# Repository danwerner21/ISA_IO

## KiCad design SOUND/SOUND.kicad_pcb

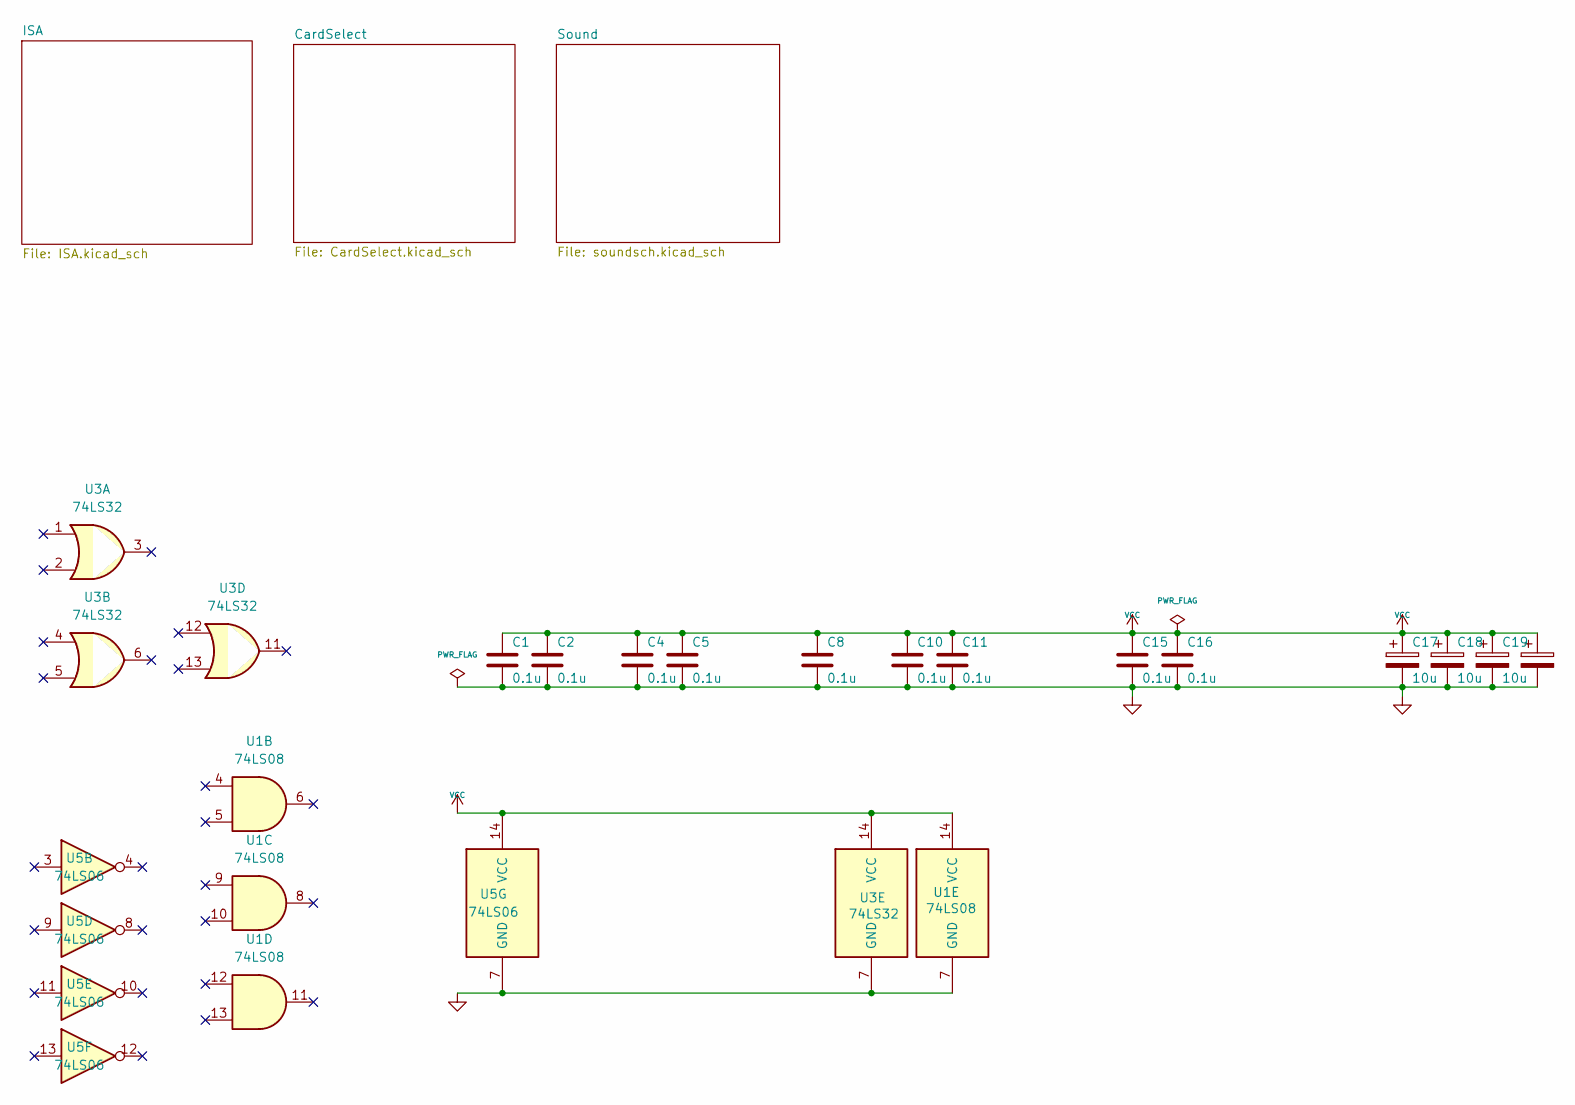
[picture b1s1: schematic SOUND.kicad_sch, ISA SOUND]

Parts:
C1, C2, C4, C5, C8, C10, C11, C15, C16: 0.1u; STD_DDW_CAP
C17, C18, C19, C20: 10u; STD_DDW_PCAP
U1: 74LS08; STD_DDW_DIP14
U3: 74LS32; STD_DDW_DIP14
U5: 74LS06; STD_DDW_DIP14

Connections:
GND: C1.2, C2.2, C4.2, C5.2, C8.2, C10.2, C11.2, C15.2, C16.2, C17.2, C18.2, C19.2, C20.2, U1.7 (GND), U3.7 (GND), U5.7 (GND); also elsewhere on the board
VCC: C1.1, C2.1, C4.1, C5.1, C8.1, C10.1, C11.1, C15.1, C16.1, C17.1, C18.1, C19.1, C20.1, U1.14 (VCC), U3.14 (VCC), U5.14 (VCC); also elsewhere on the board

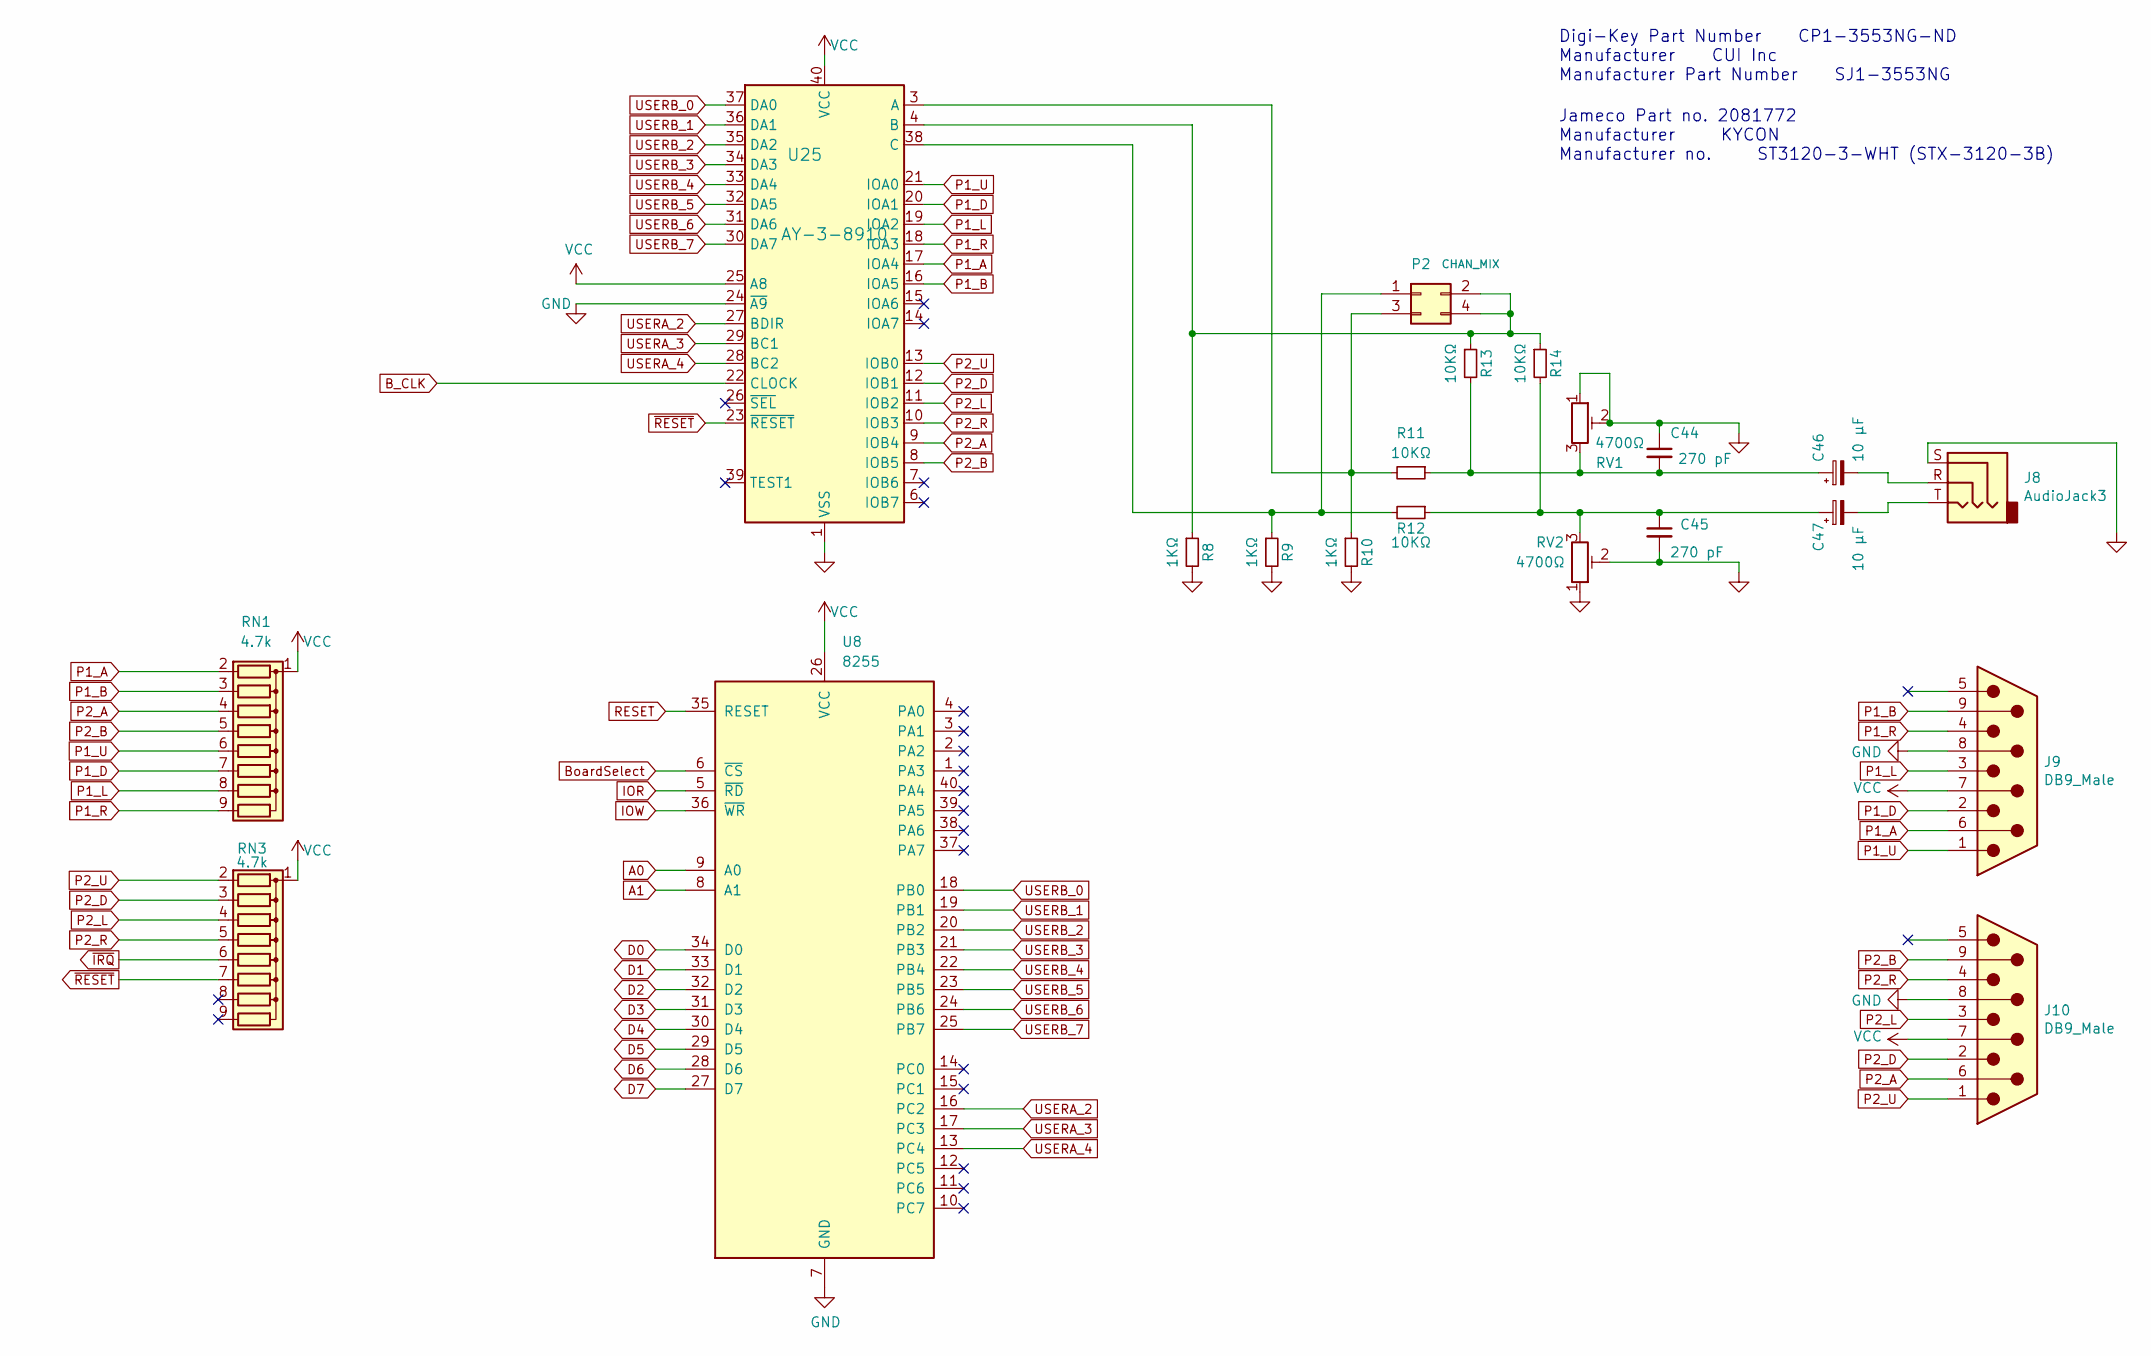
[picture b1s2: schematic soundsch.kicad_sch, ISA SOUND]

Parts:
C44, C45: 270 pF; STD_DDW_CAP
C46, C47: 10 µF; STD_DDW_PCAP
J8: AudioJack3; ddw_Jack_3.5mm_CUI_SJ1-3525N_Horizontal
J9, J10: DB9_Male; DSUB-9_Pins_Horizontal_P2.77x2.84mm_EdgePinOffset4.94mm_Hou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
P2: CHAN_MIX; PinHeader_2x02_P2.54mm_Vertical
R8, R9, R10: 1KΩ; STD_DDW_RESISTOR
R11, R12, R13, R14: 10KΩ; STD_DDW_RESISTOR
RN1, RN3: 4.7k; STD_DDW_SIP9
RV1, RV2: 4700Ω; Potentiometer_ACP_CA9-V10_Vertical
U8: 8255; STD_DDW_DIP40
U25: AY-3-8910; STD_DDW_DIP40

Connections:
A0: U8.9 (A0); also elsewhere on the board
A1: U8.8 (A1); also elsewhere on the board
B_CLK: U25.22 (CLOCK); also elsewhere on the board
BoardSelect: U8.6 (~CS); also elsewhere on the board
D0: U8.34 (D0); also elsewhere on the board
D1: U8.33 (D1); also elsewhere on the board
D2: U8.32 (D2); also elsewhere on the board
D3: U8.31 (D3); also elsewhere on the board
D4: U8.30 (D4); also elsewhere on the board
D5: U8.29 (D5); also elsewhere on the board
D6: U8.28 (D6); also elsewhere on the board
D7: U8.27 (D7); also elsewhere on the board
GND: C44.1, C45.2, J8.S, J9.8, J10.8, R8.2, R9.2, R10.2, RV1.1, RV1.2, RV2.1, RV2.2, U8.7 (GND), U25.1 (VSS), U25.24 (~A9); also elsewhere on the board
IOR: U8.5 (~RD); also elsewhere on the board
IOW: U8.36 (~WR); also elsewhere on the board
unnamed: C44.2, C46.1, R11.1, R13.2, RV1.3
unnamed: C45.1, C47.1, R12.1, R14.2, RV2.3
unnamed: C46.2, J8.R
unnamed: C47.2, J8.T
unnamed: P2.1, R9.1, R12.2, U25.38 (C)
unnamed: P2.2, P2.4, R8.1, R13.1, R14.1, U25.4 (B)
unnamed: P2.3, R10.1, R11.2, U25.3 (A)
P1_A: J9.6, RN1.2 (R1), U25.17 (IOA4)
P1_B: J9.9, RN1.3 (R2), U25.16 (IOA5)
P1_D: J9.2, RN1.7 (R6), U25.20 (IOA1)
P1_L: J9.3, RN1.8 (R7), U25.19 (IOA2)
P1_R: J9.4, RN1.9 (R8), U25.18 (IOA3)
P1_U: J9.1, RN1.6 (R5), U25.21 (IOA0)
P2_A: J10.6, RN1.4 (R3), U25.9 (IOB4)
P2_B: J10.9, RN1.5 (R4), U25.8 (IOB5)
P2_D: J10.2, RN3.3 (R2), U25.12 (IOB1)
P2_L: J10.3, RN3.4 (R3), U25.11 (IOB2)
P2_R: J10.4, RN3.5 (R4), U25.10 (IOB3)
P2_U: J10.1, RN3.2 (R1), U25.13 (IOB0)
RESET: U8.35 (RESET); also elsewhere on the board
USERA_2: U8.16 (PC2), U25.27 (BDIR)
USERA_3: U8.17 (PC3), U25.29 (BC1)
USERA_4: U8.13 (PC4), U25.28 (BC2)
USERB_0: U8.18 (PB0), U25.37 (DA0)
USERB_1: U8.19 (PB1), U25.36 (DA1)
USERB_2: U8.20 (PB2), U25.35 (DA2)
USERB_3: U8.21 (PB3), U25.34 (DA3)
USERB_4: U8.22 (PB4), U25.33 (DA4)
USERB_5: U8.23 (PB5), U25.32 (DA5)
USERB_6: U8.24 (PB6), U25.31 (DA6)
USERB_7: U8.25 (PB7), U25.30 (DA7)
VCC: J9.7, J10.7, RN1.1 (common), RN3.1 (common), U8.26 (VCC), U25.25 (A8), U25.40 (VCC); also elsewhere on the board
~IRQ: RN3.6 (R5); also elsewhere on the board
~RESET: RN3.7 (R6), U25.23 (~RESET); also elsewhere on the board

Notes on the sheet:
Jameco Part no. 2081772 Manufacturer KYCON Manufacturer no. ST3120-3-WHT (STX-3120-3B)
Digi-Key Part Number CP1-3553NG-ND Manufacturer CUI Inc Manufacturer Part Number SJ1-3553NG

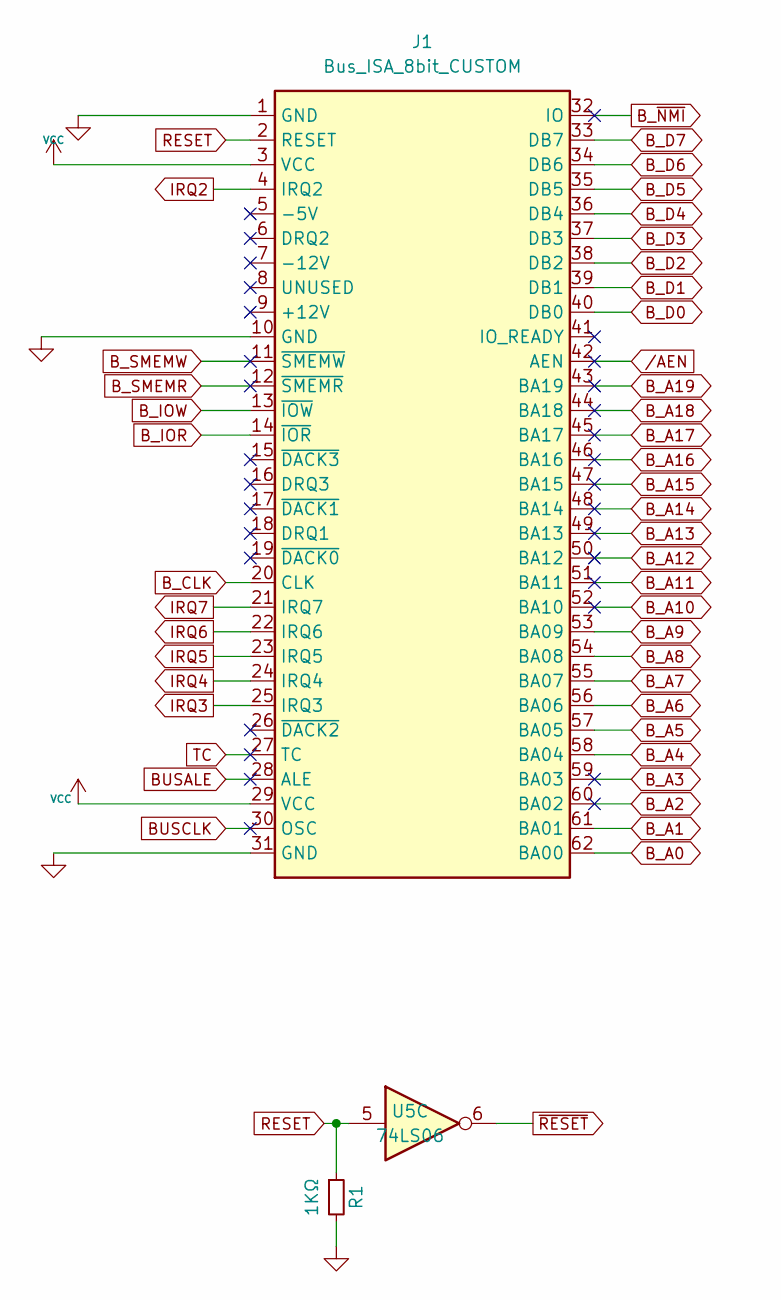
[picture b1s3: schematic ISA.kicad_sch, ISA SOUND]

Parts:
J1: Bus_ISA_8bit_CUSTOM; BUSEDGE_XT
R1: 1KΩ; STD_DDW_RESISTOR
U5: 74LS06; STD_DDW_DIP14

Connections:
BUSALE: J1.28 (ALE)
BUSCLK: J1.30 (OSC)
B_A0: J1.62 (BA00); also elsewhere on the board
B_A1: J1.61 (BA01); also elsewhere on the board
B_A2: J1.60 (BA02)
B_A3: J1.59 (BA03)
B_A4: J1.58 (BA04); also elsewhere on the board
B_A5: J1.57 (BA05); also elsewhere on the board
B_A6: J1.56 (BA06); also elsewhere on the board
B_A7: J1.55 (BA07); also elsewhere on the board
B_A8: J1.54 (BA08); also elsewhere on the board
B_A9: J1.53 (BA09); also elsewhere on the board
B_A10: J1.52 (BA10)
B_A11: J1.51 (BA11)
B_A12: J1.50 (BA12)
B_A13: J1.49 (BA13)
B_A14: J1.48 (BA14)
B_A15: J1.47 (BA15)
B_A16: J1.46 (BA16)
B_A17: J1.45 (BA17)
B_A18: J1.44 (BA18)
B_A19: J1.43 (BA19)
B_CLK: J1.20 (CLK); also elsewhere on the board
B_D0: J1.40 (DB0); also elsewhere on the board
B_D1: J1.39 (DB1); also elsewhere on the board
B_D2: J1.38 (DB2); also elsewhere on the board
B_D3: J1.37 (DB3); also elsewhere on the board
B_D4: J1.36 (DB4); also elsewhere on the board
B_D5: J1.35 (DB5); also elsewhere on the board
B_D6: J1.34 (DB6); also elsewhere on the board
B_D7: J1.33 (DB7); also elsewhere on the board
B_IOR: J1.14 (~IOR); also elsewhere on the board
B_IOW: J1.13 (~IOW); also elsewhere on the board
B_SMEMR: J1.12 (~SMEMR)
B_SMEMW: J1.11 (~SMEMW)
B_~NMI: J1.32 (IO)
GND: J1.1 (GND), J1.10 (GND), J1.31 (GND), R1.2; also elsewhere on the board
IRQ2: J1.4 (IRQ2); also elsewhere on the board
IRQ3: J1.25 (IRQ3); also elsewhere on the board
IRQ4: J1.24 (IRQ4); also elsewhere on the board
IRQ5: J1.23 (IRQ5); also elsewhere on the board
IRQ6: J1.22 (IRQ6); also elsewhere on the board
IRQ7: J1.21 (IRQ7); also elsewhere on the board
RESET: J1.2 (RESET), R1.1, U5.5; also elsewhere on the board
TC: J1.27 (TC)
VCC: J1.3 (VCC), J1.29 (VCC); also elsewhere on the board
/AEN: J1.42 (AEN)
~RESET: U5.6; also elsewhere on the board

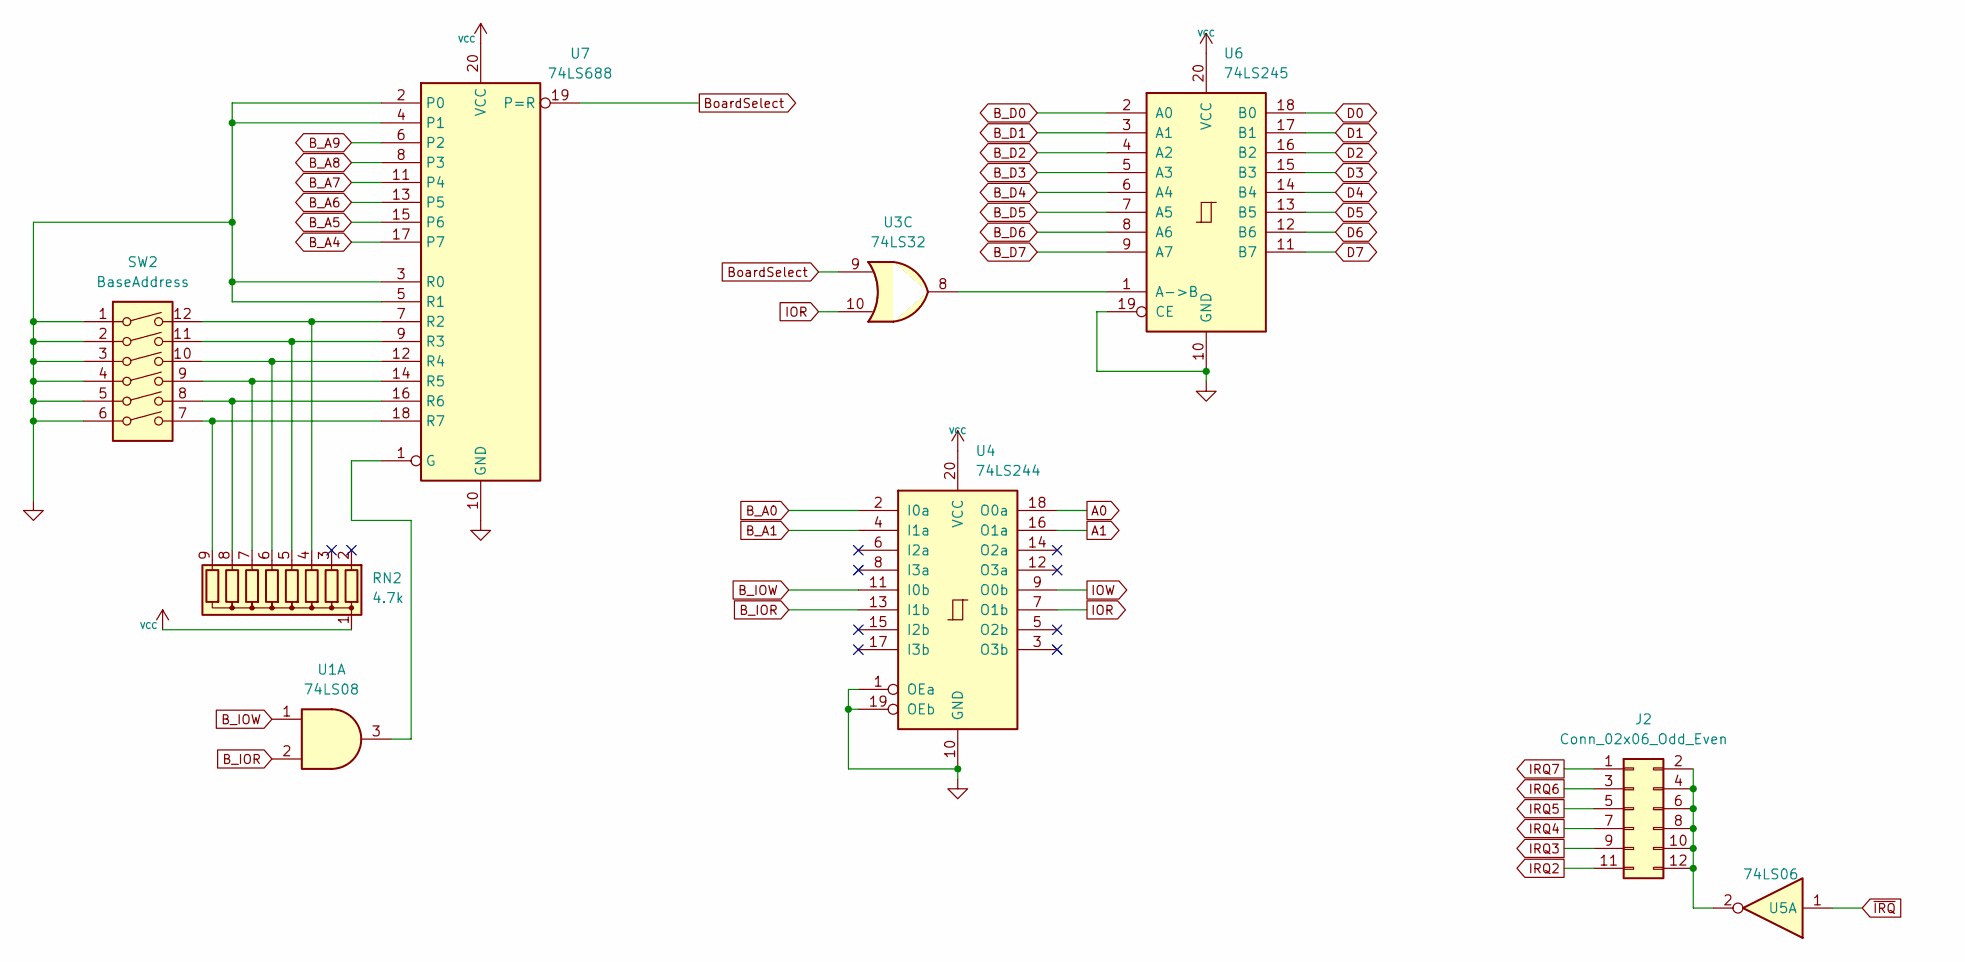
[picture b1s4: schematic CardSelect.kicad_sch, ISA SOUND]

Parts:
J2: Conn_02x06_Odd_Even; STD_DDW_PINHEAD_V_2x06
RN2: 4.7k; STD_DDW_SIP9
SW2: BaseAddress; DIP-12_W7.62mm_Socket_LongPads
U1: 74LS08; STD_DDW_DIP14
U3: 74LS32; STD_DDW_DIP14
U4: 74LS244; STD_DDW_DIP20
U5: 74LS06; STD_DDW_DIP14
U6: 74LS245; STD_DDW_DIP20
U7: 74LS688; STD_DDW_DIP20

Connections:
A0: U4.18 (O0a); also elsewhere on the board
A1: U4.16 (O1a); also elsewhere on the board
B_A0: U4.2 (I0a); also elsewhere on the board
B_A1: U4.4 (I1a); also elsewhere on the board
B_A4: U7.17 (P7); also elsewhere on the board
B_A5: U7.15 (P6); also elsewhere on the board
B_A6: U7.13 (P5); also elsewhere on the board
B_A7: U7.11 (P4); also elsewhere on the board
B_A8: U7.8 (P3); also elsewhere on the board
B_A9: U7.6 (P2); also elsewhere on the board
B_D0: U6.2 (A0); also elsewhere on the board
B_D1: U6.3 (A1); also elsewhere on the board
B_D2: U6.4 (A2); also elsewhere on the board
B_D3: U6.5 (A3); also elsewhere on the board
B_D4: U6.6 (A4); also elsewhere on the board
B_D5: U6.7 (A5); also elsewhere on the board
B_D6: U6.8 (A6); also elsewhere on the board
B_D7: U6.9 (A7); also elsewhere on the board
B_IOR: U1.2, U4.13 (I1b); also elsewhere on the board
B_IOW: U1.1, U4.11 (I0b); also elsewhere on the board
BoardSelect: U3.9, U7.19 (P=R); also elsewhere on the board
D0: U6.18 (B0); also elsewhere on the board
D1: U6.17 (B1); also elsewhere on the board
D2: U6.16 (B2); also elsewhere on the board
D3: U6.15 (B3); also elsewhere on the board
D4: U6.14 (B4); also elsewhere on the board
D5: U6.13 (B5); also elsewhere on the board
D6: U6.12 (B6); also elsewhere on the board
D7: U6.11 (B7); also elsewhere on the board
GND: SW2.1, SW2.2, SW2.3, SW2.4, SW2.5, SW2.6, U4.1 (OEa), U4.10 (GND), U4.19 (OEb), U6.10 (GND), U6.19 (CE), U7.2 (P0), U7.3 (R0), U7.4 (P1), U7.5 (R1), U7.10 (GND); also elsewhere on the board
IOR: U3.10, U4.7 (O1b); also elsewhere on the board
IOW: U4.9 (O0b); also elsewhere on the board
IRQ2: J2.11; also elsewhere on the board
IRQ3: J2.9; also elsewhere on the board
IRQ4: J2.7; also elsewhere on the board
IRQ5: J2.5; also elsewhere on the board
IRQ6: J2.3; also elsewhere on the board
IRQ7: J2.1; also elsewhere on the board
unnamed: J2.2, J2.4, J2.6, J2.8, J2.10, J2.12, U5.2
unnamed: RN2.4 (R3), SW2.12, U7.7 (R2)
unnamed: RN2.5 (R4), SW2.11, U7.9 (R3)
unnamed: RN2.6 (R5), SW2.10, U7.12 (R4)
unnamed: RN2.7 (R6), SW2.9, U7.14 (R5)
unnamed: RN2.8 (R7), SW2.8, U7.16 (R6)
unnamed: RN2.9 (R8), SW2.7, U7.18 (R7)
unnamed: U3.8, U6.1 (A->B)
unnamed: U1.3, U7.1 (G)
VCC: RN2.1 (common), U4.20 (VCC), U6.20 (VCC), U7.20 (VCC); also elsewhere on the board
~IRQ: U5.1; also elsewhere on the board

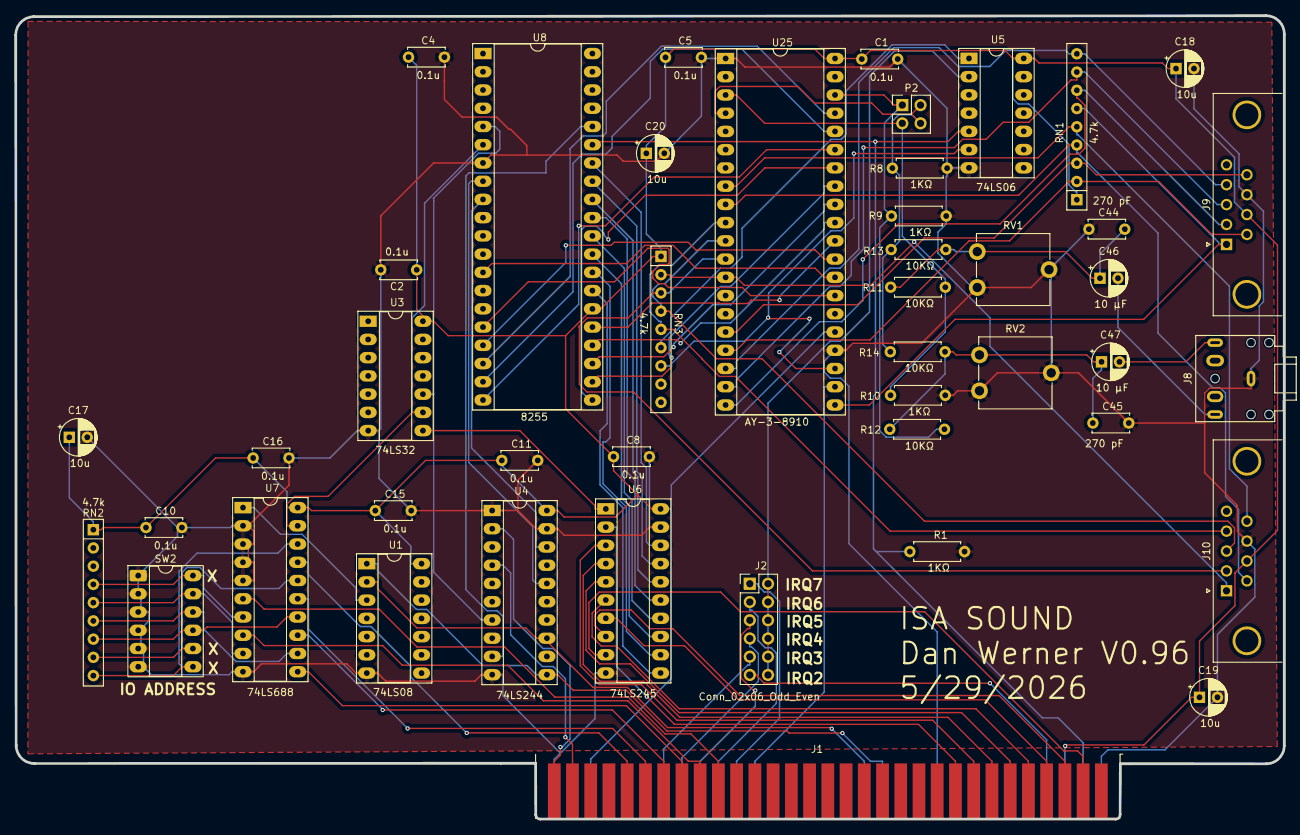
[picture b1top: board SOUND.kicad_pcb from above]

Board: 2 copper layers, 176.7 x 111.9 mm, 45 parts (0 on the bottom side), 82 nets.

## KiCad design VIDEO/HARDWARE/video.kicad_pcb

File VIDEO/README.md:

F8000 - window
3e0 - SID

;;; 	VRAM Memory Map
;;;	$1000-$177F	40/80 Text Page 1
;;;	$1800-$1F7F	40/80 Color Page 1
;;;	$2000-$277F	40/80 Text Page 2
;;;	$2800-$2F7F	40/80 Color Page 2
;;;	$2000-$5FFF	HIRES PAGE 1
;;;	$6000-$8FFF	HIRES PAGE 2
;;;	$2000-$BFFF	DOUBLE HIRES

  $0x00 0x01=soft_scanline_emulation, 0x02 nO soft_scanline_emulatioN
  $0x01 0x01=page1, 0x02 page2
  $0x02  character generator write offset (data << 3)
  $0x03 character generator write DATA
  $0x04 EXECUTE device command
        0x00- reset to the default configuration
        0x01- reset to the saved configuration
	0x02- save the current configuration

  $0x05  0x01=soft_text=true, 0x02=soft_text=false
  $0x06 Lores Mode=0X01,NO lores Mode=0x02
  $0x07 Double Lores Mode=0X01,NO Double lores Mode=0x02
  $0x08 Hires Mode=0X01,NO Hires Mode=0x02
  $0x09 Double Hires Mode=0X01,NO Double Hires lores Mode=0x02
  $0x0A 80COL Mode=0X01,NO 80COL Mode=0x02
  $0x0B MIXED Mode=0X01,NO MIXED Mode=0x02
  $0x0C QUAD Hires Mode=0X01,NO QUAD Hires lores Mode=0x02
  $0x0D MONO Hires Mode=0X01,NO MONO Hires lores Mode=0x02

>EFE2 00
>EFE1 03
>EFD0 00 01 02 03 04 05 06 07
>EFD8 F8 F9 FA FB 0C 0D 0E 0F
>EFE0 03
>EFE2 01

>9000 65 66 67 68 69 70 71 72
>9800 12 13 32 23 43 45 54 31

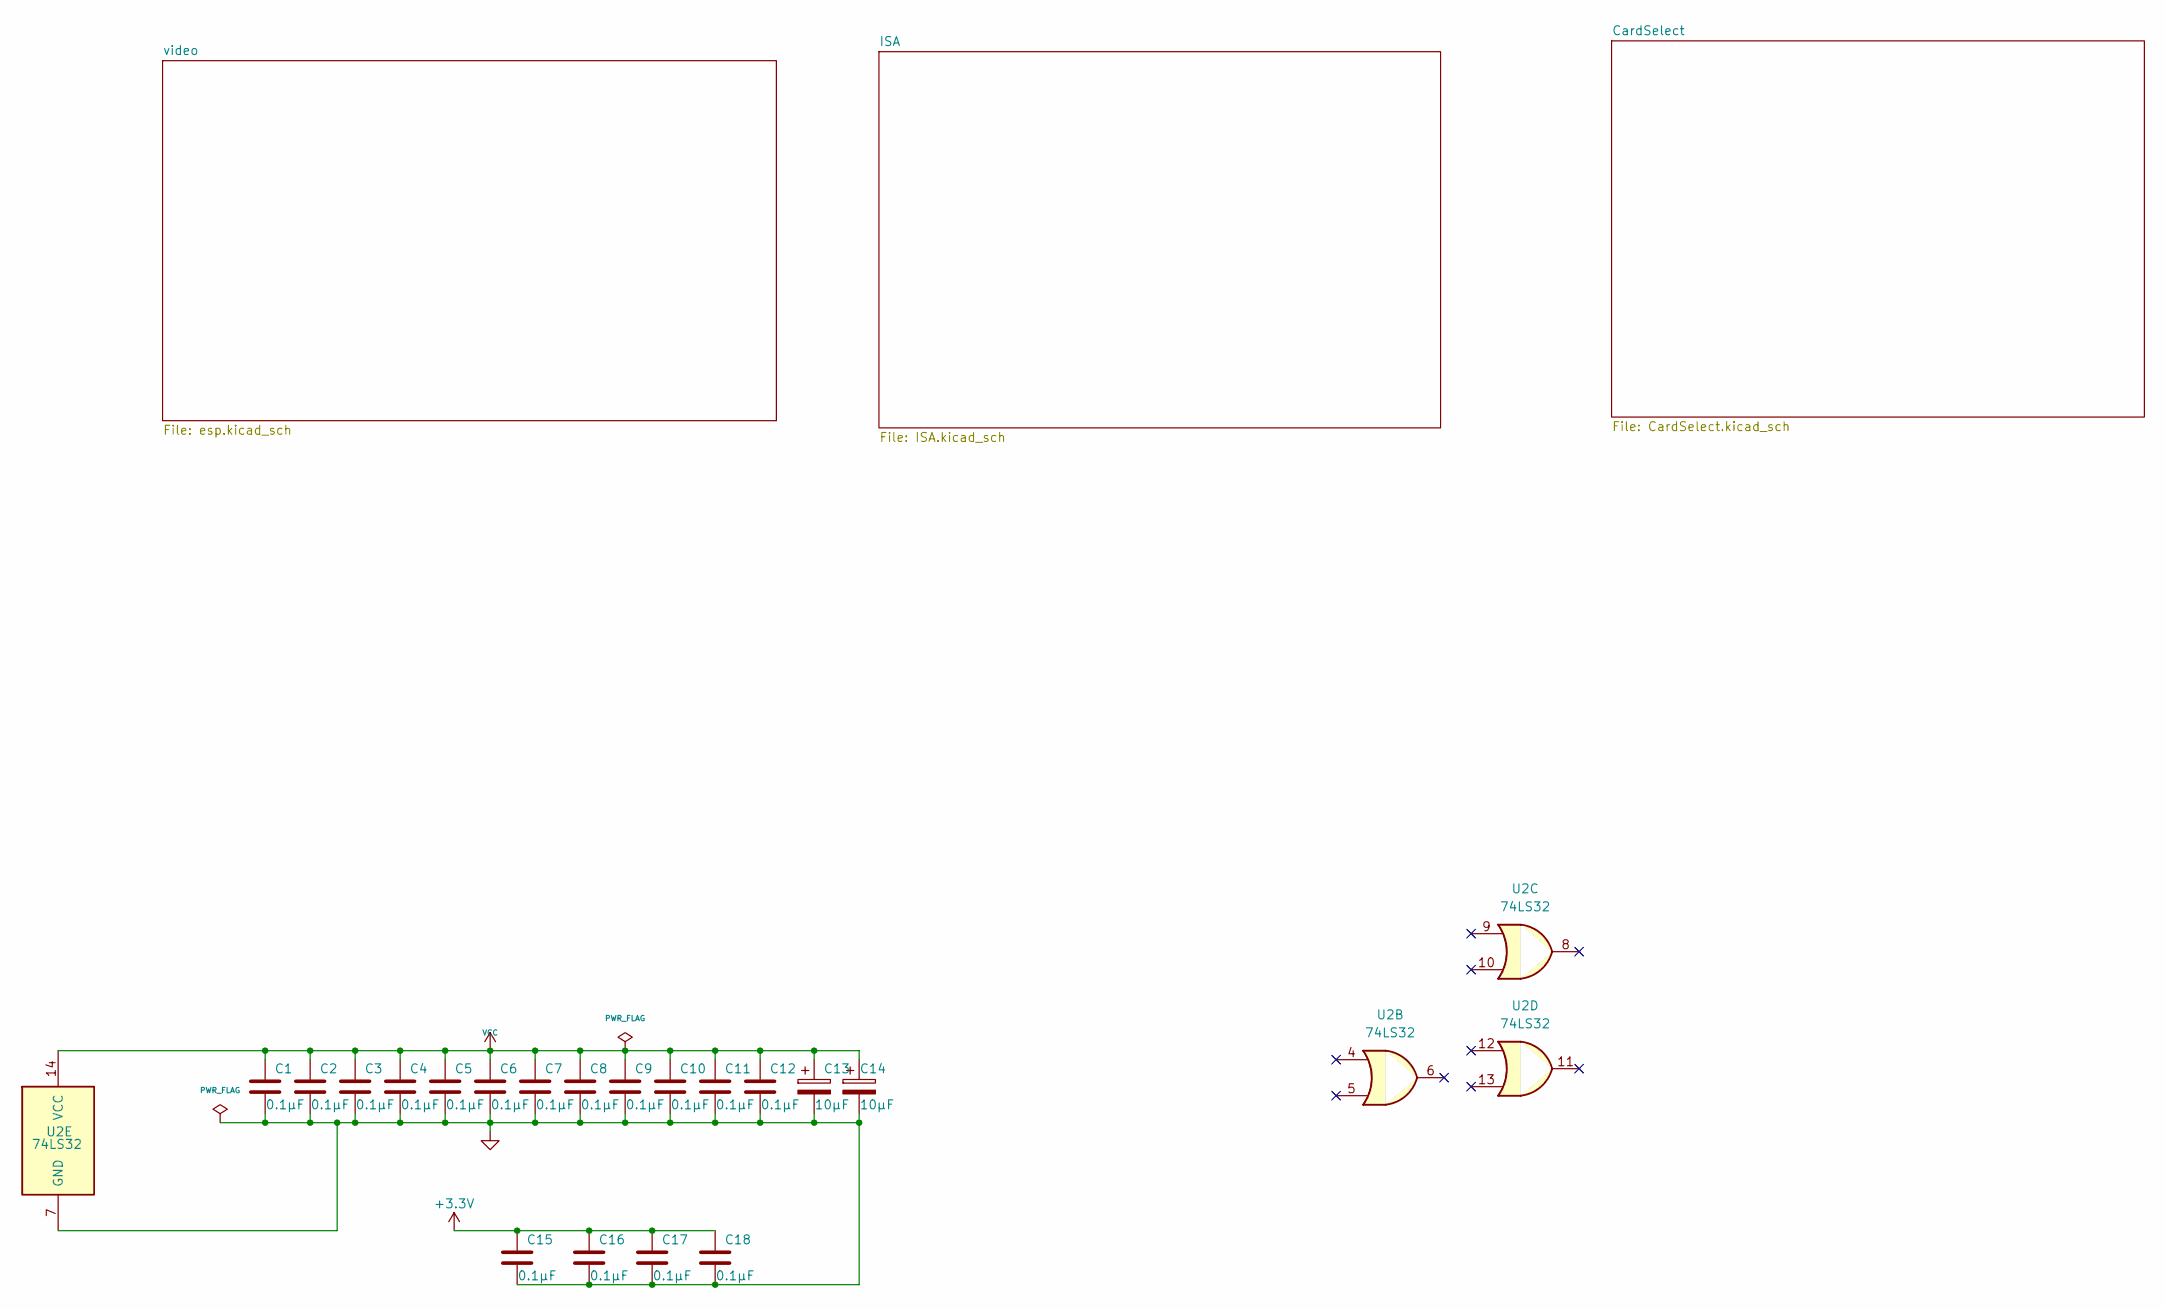
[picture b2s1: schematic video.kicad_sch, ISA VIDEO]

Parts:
C1, C2, C3, C4, C5, C6, C7, C8, C9, C10, C11, C12, C15, C16, C17, C18: 0.1µF; STD_DDW_CAP
C13, C14: 10µF; STD_DDW_PCAP
U2: 74LS32; STD_DDW_DIP14

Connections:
+3.3V: C15.1, C16.1, C17.1, C18.1; also elsewhere on the board
GND: C1.2, C2.2, C3.2, C4.2, C5.2, C6.2, C7.2, C8.2, C9.2, C10.2, C11.2, C12.2, C13.2, C14.2, C15.2, C16.2, C17.2, C18.2, U2.7 (GND); also elsewhere on the board
VCC: C1.1, C2.1, C3.1, C4.1, C5.1, C6.1, C7.1, C8.1, C9.1, C10.1, C11.1, C12.1, C13.1, C14.1, U2.14 (VCC); also elsewhere on the board

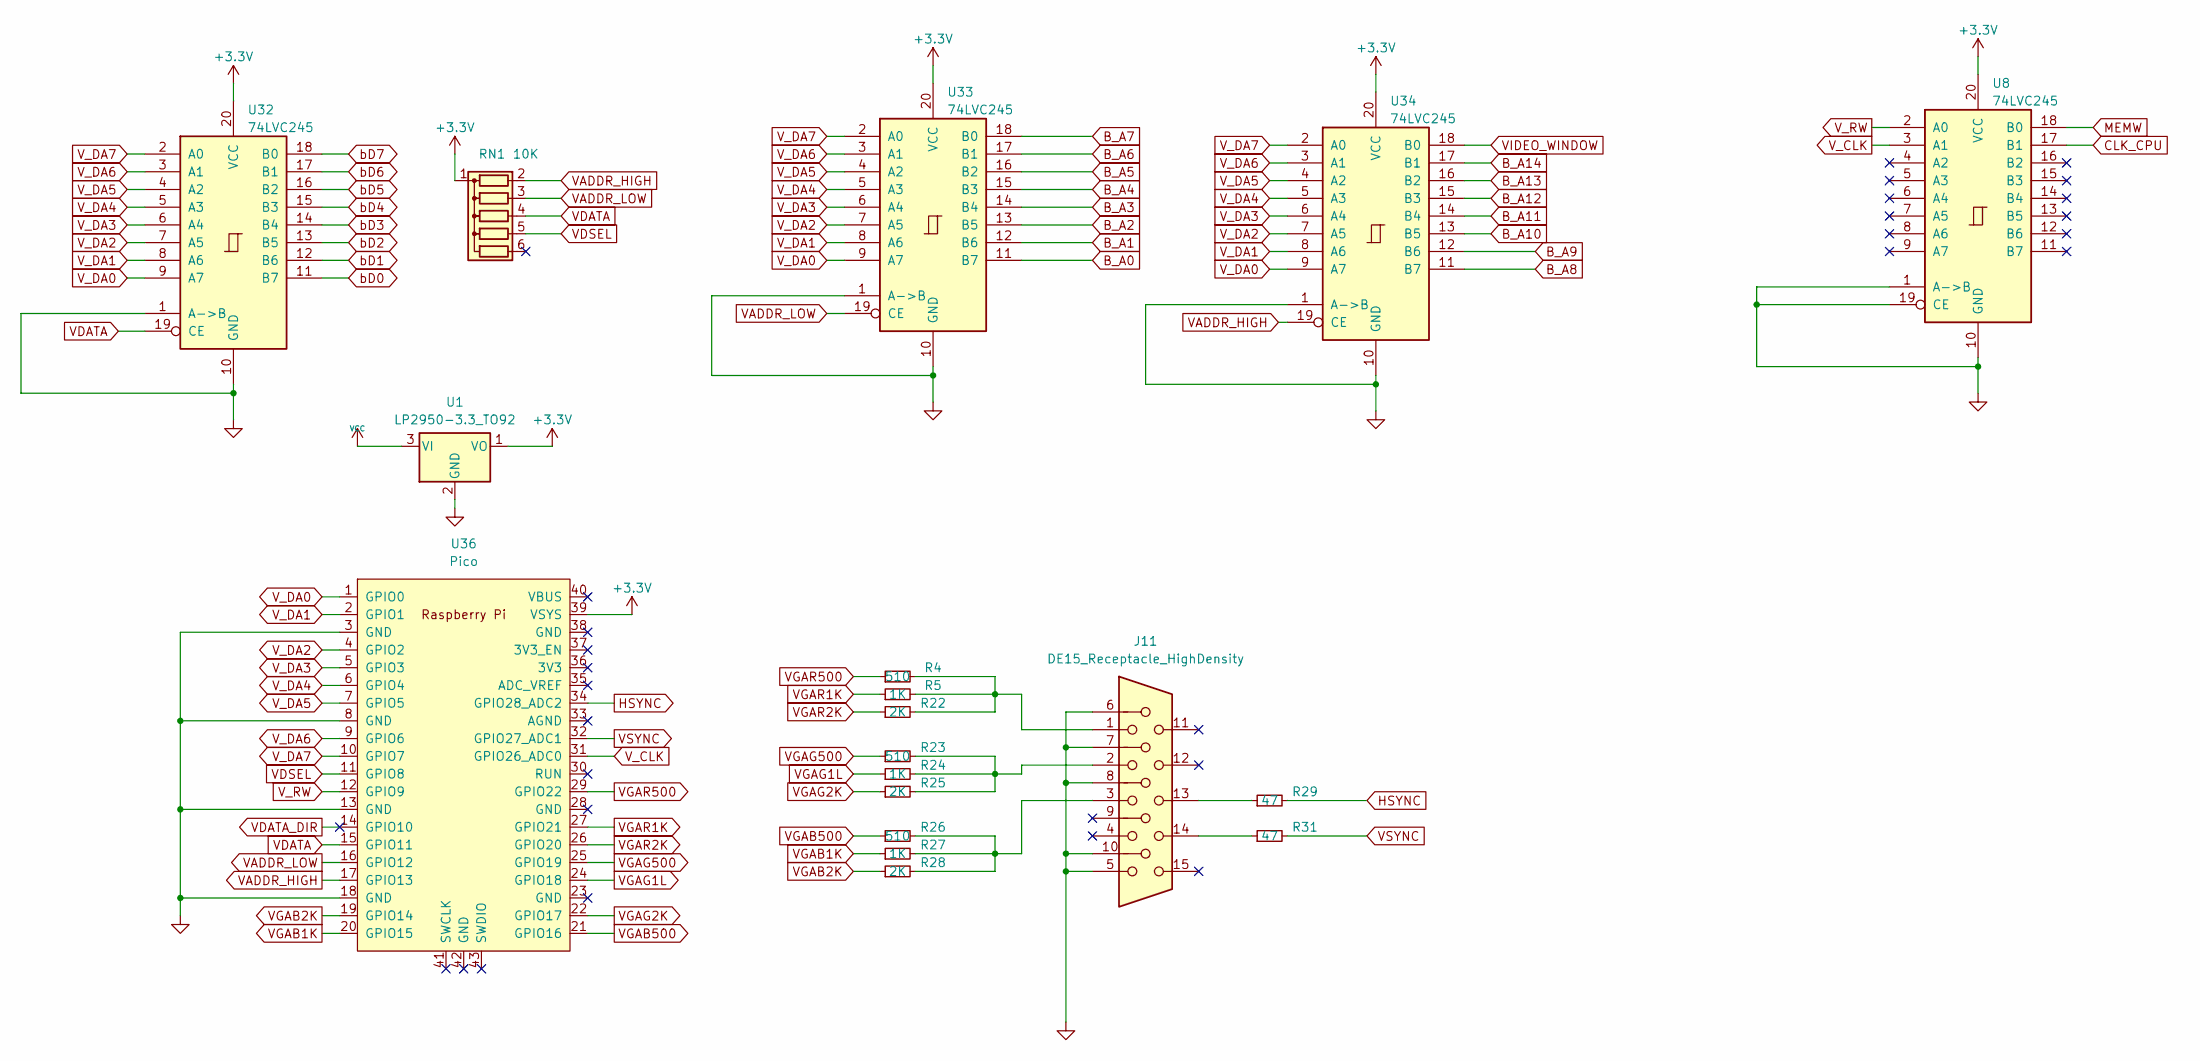
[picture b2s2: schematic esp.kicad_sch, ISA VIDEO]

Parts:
J11: DE15_Receptacle_HighDensity; STD_DDW_VGA
R4, R23, R26: 510; STD_DDW_RESISTOR
R5, R24, R27: 1K; STD_DDW_RESISTOR
R22, R25, R28: 2K; STD_DDW_RESISTOR
R29, R31: 47; STD_DDW_RESISTOR
RN1: 10K; R_Array_SIP6
U1: LP2950-3.3_TO92; TO-92_Inline
U8, U32, U33, U34: 74LVC245; STD_DDW_DIP20
U36: Pico; RPi_Pico_SMD_TH_DDW

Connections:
+3.3V: RN1.1 (common), U1.1 (VO), U8.20 (VCC), U32.20 (VCC), U33.20 (VCC), U34.20 (VCC), U36.39 (VSYS); also elsewhere on the board
B_A0: U33.11 (B7); also elsewhere on the board
B_A1: U33.12 (B6); also elsewhere on the board
B_A2: U33.13 (B5); also elsewhere on the board
B_A3: U33.14 (B4); also elsewhere on the board
B_A4: U33.15 (B3); also elsewhere on the board
B_A5: U33.16 (B2); also elsewhere on the board
B_A6: U33.17 (B1); also elsewhere on the board
B_A7: U33.18 (B0); also elsewhere on the board
B_A8: U34.11 (B7); also elsewhere on the board
B_A9: U34.12 (B6); also elsewhere on the board
B_A10: U34.13 (B5); also elsewhere on the board
B_A11: U34.14 (B4); also elsewhere on the board
B_A12: U34.15 (B3); also elsewhere on the board
B_A13: U34.16 (B2); also elsewhere on the board
B_A14: U34.17 (B1); also elsewhere on the board
CLK_CPU: U8.17 (B1); also elsewhere on the board
GND: J11.5, J11.6, J11.7, J11.8, J11.10, U1.2 (GND), U8.1 (A->B), U8.10 (GND), U8.19 (CE), U32.1 (A->B), U32.10 (GND), U33.1 (A->B), U33.10 (GND), U34.1 (A->B), U34.10 (GND), U36.3 (GND), U36.8 (GND), U36.13 (GND), U36.18 (GND); also elsewhere on the board
HSYNC: R29.2, U36.34 (GPIO28_ADC2)
MEMW: U8.18 (B0); also elsewhere on the board
unnamed: J11.1, R4.2, R5.2, R22.2
unnamed: J11.2, R23.2, R24.2, R25.2
unnamed: J11.3, R26.2, R27.2, R28.2
unnamed: J11.13, R29.1
unnamed: J11.14, R31.1
VADDR_HIGH: RN1.2 (R1), U34.19 (CE), U36.17 (GPIO13)
VADDR_LOW: RN1.3 (R2), U33.19 (CE), U36.16 (GPIO12)
VCC: U1.3 (VI); also elsewhere on the board
VDATA: RN1.4 (R3), U32.19 (CE), U36.15 (GPIO11)
VDATA_DIR: U36.14 (GPIO10)
VDATA_DIR_1: U36.14 (GPIO10)
VDSEL: RN1.5 (R4), U36.11 (GPIO8)
VGAB1K: R27.1, U36.20 (GPIO15)
VGAB2K: R28.1, U36.19 (GPIO14)
VGAB500: R26.1, U36.21 (GPIO16)
VGAG1L: R24.1, U36.24 (GPIO18)
VGAG2K: R25.1, U36.22 (GPIO17)
VGAG500: R23.1, U36.25 (GPIO19)
VGAR1K: R5.1, U36.27 (GPIO21)
VGAR2K: R22.1, U36.26 (GPIO20)
VGAR500: R4.1, U36.29 (GPIO22)
VIDEO_WINDOW: U34.18 (B0); also elsewhere on the board
VSYNC: R31.2, U36.32 (GPIO27_ADC1)
V_CLK: U8.3 (A1), U36.31 (GPIO26_ADC0)
V_DA0: U32.9 (A7), U33.9 (A7), U34.9 (A7), U36.1 (GPIO0)
V_DA1: U32.8 (A6), U33.8 (A6), U34.8 (A6), U36.2 (GPIO1)
V_DA2: U32.7 (A5), U33.7 (A5), U34.7 (A5), U36.4 (GPIO2)
V_DA3: U32.6 (A4), U33.6 (A4), U34.6 (A4), U36.5 (GPIO3)
V_DA4: U32.5 (A3), U33.5 (A3), U34.5 (A3), U36.6 (GPIO4)
V_DA5: U32.4 (A2), U33.4 (A2), U34.4 (A2), U36.7 (GPIO5)
V_DA6: U32.3 (A1), U33.3 (A1), U34.3 (A1), U36.9 (GPIO6)
V_DA7: U32.2 (A0), U33.2 (A0), U34.2 (A0), U36.10 (GPIO7)
V_RW: U8.2 (A0), U36.12 (GPIO9)
bD0: U32.11 (B7); also elsewhere on the board
bD1: U32.12 (B6); also elsewhere on the board
bD2: U32.13 (B5); also elsewhere on the board
bD3: U32.14 (B4); also elsewhere on the board
bD4: U32.15 (B3); also elsewhere on the board
bD5: U32.16 (B2); also elsewhere on the board
bD6: U32.17 (B1); also elsewhere on the board
bD7: U32.18 (B0); also elsewhere on the board
